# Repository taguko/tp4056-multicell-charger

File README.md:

# TP4056 Multicell Charger

A USB Type-C powered charger for small 2S/3S LiPo and Li-ion battery packs.

This project was designed to provide a simple and convenient way to charge small multicell batteries without using a full-featured RC balance charger.

## Prototype

## Features

- USB Type-C input
- Supports 2S and 3S LiPo / Li-ion battery packs
- Independent CC/CV charging for each cell
- Approximately 120mA charging current per cell
- TP4056-based charging channels
- Isolated DC/DC converters for upper cells
- No conventional balancing circuit required

## Recommended Battery Capacity

100mAh - 300mAh

The charging current is approximately 120mA per cell. This corresponds to about 1C charging for a 120mAh battery and about 0.4C for a 300mAh battery.

## Charging Current

Each charging channel is configured for approximately 120mA using a 10kΩ PROG resistor.

## Concept

Conventional multicell chargers charge the entire battery pack while balancing cell voltages using a balancing circuit.

This project takes a different approach. Each cell is charged independently using its own TP4056 charger.

Because the cells inside a 2S/3S pack are connected in series, each TP4056 charger must operate in an isolated power domain. Isolated DC/DC converters allow multiple TP4056 channels to charge different cells independently.

As a result, cell voltages naturally converge without requiring a conventional balancing circuit.

```mermaid
flowchart LR

USB["USB-C 5V"]

USB --> TP1["TP4056<br/>Cell1"]
USB --> ISO2["B0505S-1W<br/>Cell2"]
USB --> ISO3["B0505S-1W<br/>Cell3"]

ISO2 --> TP2["TP4056<br/>Cell2"]
ISO3 --> TP3["TP4056<br/>Cell3"]

TP1 --> C1["Cell1"]
TP2 --> C2["Cell2"]
TP3 --> C3["Cell3"]

C1 --> PACK["2S/3S LiPo・Li-ion Pack"]
C2 --> PACK
C3 --> PACK
```

## BOM
[PartsCabi.net](https://partscabi.net/list/6ee6419b-a65a-492d-b7c7-b3cb2271a9e4)

## Limitations

- This charger assumes that all cells are in reasonable condition and have similar characteristics.
- Cell voltage balance may vary depending on differences in cell aging, internal resistance, capacity, and self-discharge rate.
- Perfect cell balancing under all conditions is not guaranteed.
- This project is intended for users who understand the operating principles and limitations of Li-ion/LiPo charging circuits.
- Users are expected to review the schematic and evaluate the design themselves before use.

## Safety Notice

- For LiPo and Li-ion batteries only.
- Do not use damaged batteries.
- Never leave batteries unattended while charging.
- Do not connect batteries to both the 2-cell and 3-cell connectors simultaneously.
- Verify connector polarity before use.
- Use this project at your own risk.

## Disclaimer

This project is provided for educational, experimental, and research purposes only.

Lithium battery charging involves inherent risks. The author assumes no responsibility for any damage, injury, or loss resulting from the use of this project.

## License

MIT License

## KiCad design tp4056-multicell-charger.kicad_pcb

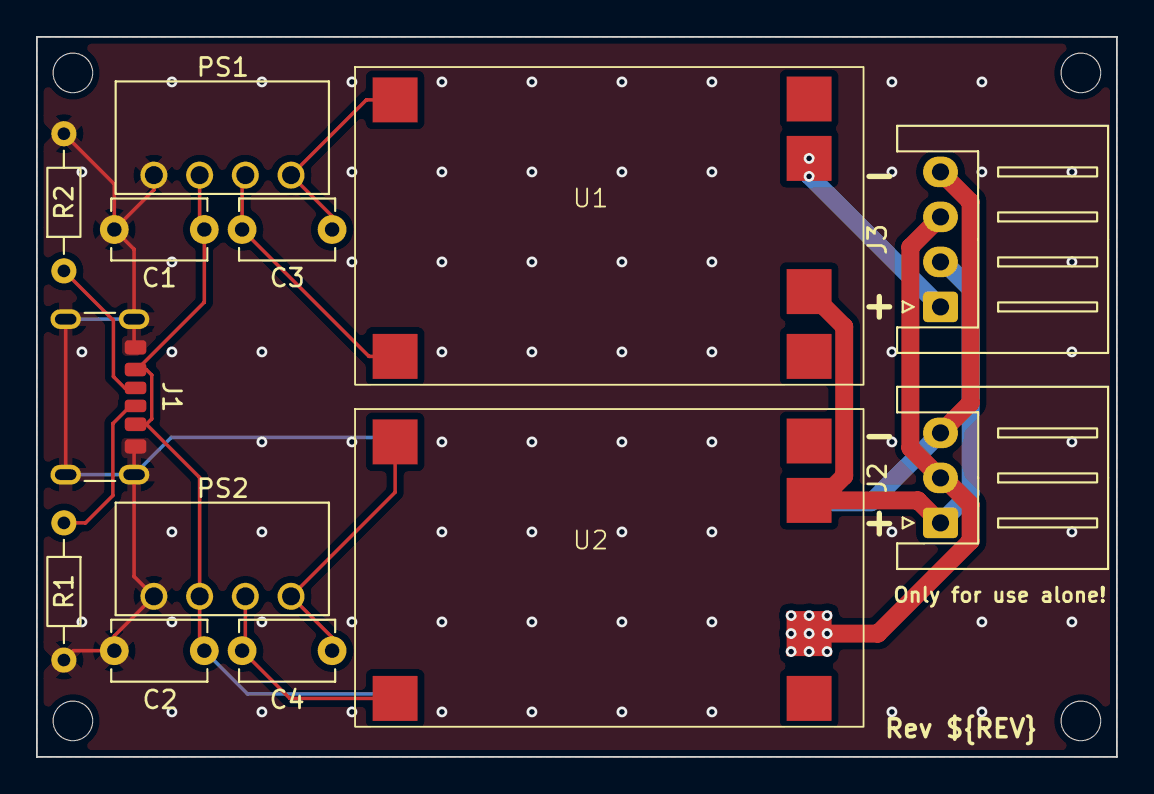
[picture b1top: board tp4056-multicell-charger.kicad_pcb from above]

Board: 2 copper layers, 60.0 x 40.0 mm, 14 parts (1 on the bottom side), 12 nets.

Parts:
C1, C2: 4μ7F/16V; C_Disc_D5.1mm_W3.2mm_P5.00mm
C3, C4: 10μF/16V; C_Disc_D5.1mm_W3.2mm_P5.00mm
J1: USB_C_Receptacle_PowerOnly_6P; USB_C_Receptacle_GCT_USB4125-xx-x_6P_TopMnt_Horizontal
J2: Conn_01x03; JST_XH_S3B-XH-A_1x03_P2.50mm_Horizontal
J3: Conn_01x04; JST_XH_S4B-XH-A_1x04_P2.50mm_Horizontal
PS1, PS2: B0505S-1W; Converter_DCDC_B_S-1WR3 Series
R1, R2: 5k1Ω; R_Axial_DIN0204_L3.6mm_D1.6mm_P7.62mm_Horizontal
U1, U2, U3: TP4056; TP4056_Module_SMD

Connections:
+5V: C1.2, C2.2, J1.A9 (VBUS), J1.B9 (VBUS), PS1.2 (Vin), PS2.2 (Vin), U3.1 (+)
Cell1+: J2.2, J3.3, U2.4 (B-), U3.5 (B+)
Cell1-: J2.3, J3.4, U3.4 (B-)
Cell2+: J2.1, J3.2, U1.4 (B-), U2.5 (B+)
Cell3+: J3.1, U1.5 (B+)
GND: C1.1, C2.1, J1.A12 (GND), J1.B12 (GND), J1.SH (SHIELD), PS1.1 (GND), PS2.1 (GND), R1.2, R2.2, U3.2 (-)
unnamed: J1.A5 (CC1), R2.1
unnamed: J1.B5 (CC2), R1.1
unnamed: C3.1, PS1.3 (0V), U1.2 (-)
unnamed: C3.2, PS1.4 (+Vo), U1.1 (+)
unnamed: C4.1, PS2.3 (0V), U2.2 (-)
unnamed: C4.2, PS2.4 (+Vo), U2.1 (+)
